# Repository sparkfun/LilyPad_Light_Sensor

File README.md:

LilyPad Light Sensor
========================================

[*LilyPad Light Sensor(DEV-14629)*](https://www.sparkfun.com/products/14629)

This is a simple to use light sensor that outputs an analog value from 0 to 5V. 
With exposure to daylight, this sensor will output 5V. 
Covering the sensor with your hand, the sensor will output 0V. 
In a normal indoor lighting situation, the sensor will output from 1 to 2V.

Repository Contents
-------------------
* **/Firmware** - Arduino Example Code
* **/Hardware** - Eagle design files (.brd, .sch)
* **/Production** - Production panel files (.brd)

Documentation
--------------
* **[Hookup Guide](https://learn.sparkfun.com/tutorials/lilypad-light-sensor-v2-hookup-guide)** - Basic hookup guide for the LilyPad Light Sensor.
* **[SparkFun Fritzing repo](https://github.com/sparkfun/Fritzing_Parts)** - Fritzing diagrams for SparkFun products.
* **[SparkFun 3D Model repo](https://github.com/sparkfun/3D_Models)** - 3D models of SparkFun products. 

License Information
-------------------
This product is _**open source**_! 

The **hardware** is released under [Creative Commons ShareAlike 4.0 International](https://creativecommons.org/licenses/by-sa/4.0/).

Please use, reuse, and modify these files as you see fit. Please maintain attribution to SparkFun Electronics and release anything derivative under the same license.

Distributed as-is; no warranty is given.

- Your friends at SparkFun.

_**Note:** A portion of this sale is given back to Dr. Leah Buechley for continued development and education of e-textiles._

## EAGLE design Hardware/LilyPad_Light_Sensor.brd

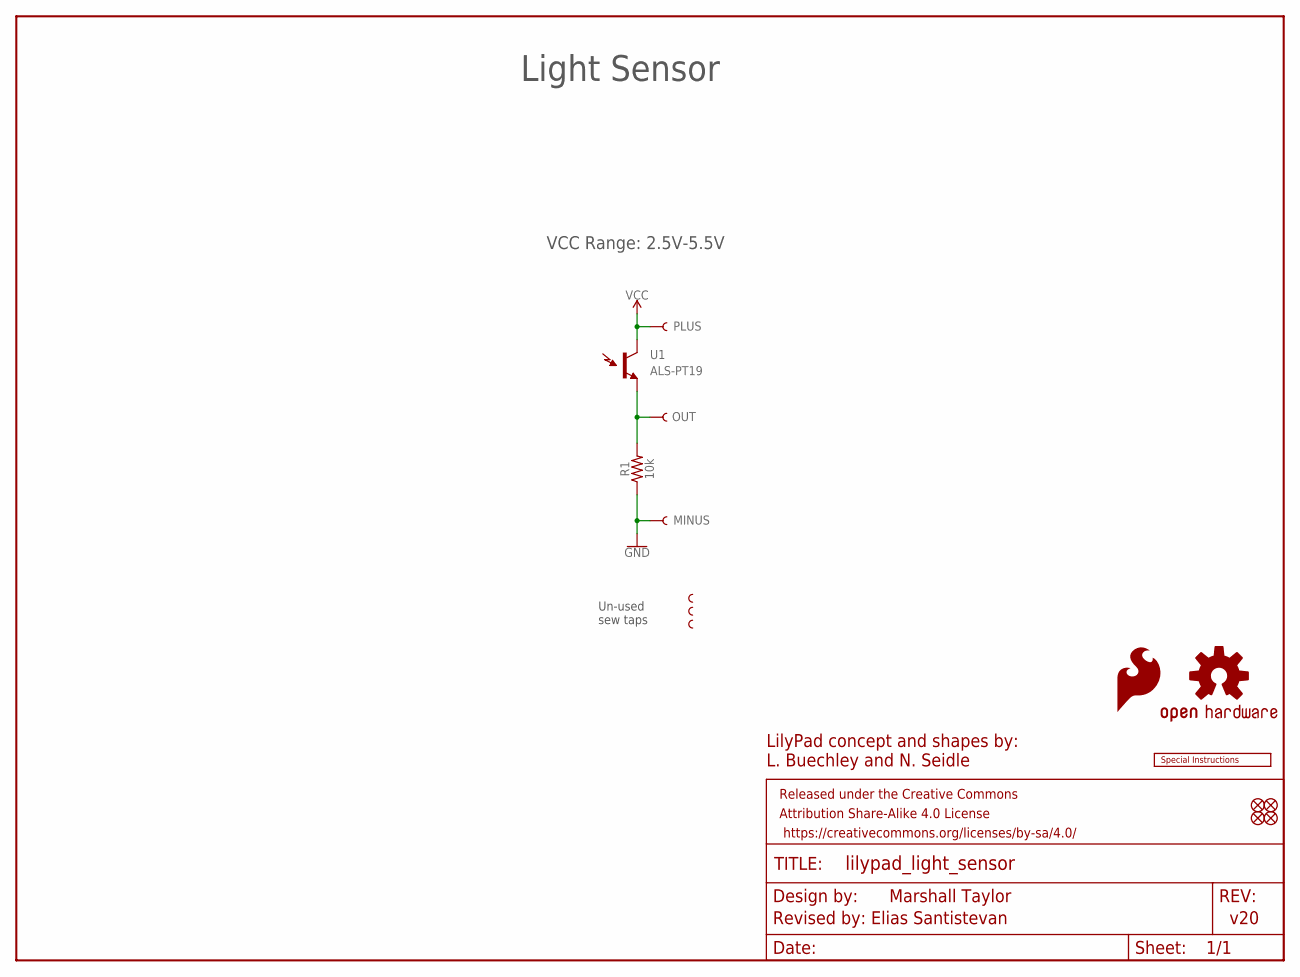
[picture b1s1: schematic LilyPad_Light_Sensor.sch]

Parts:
FD1, FD2, FD3, FD4: FIDUCIALUFIDUCIAL; FIDUCIAL-MICRO
FRAME2: FRAME-LETTER; CREATIVE_COMMONS
LOGO1: OSHW-LOGOMINI; OSHW-LOGO-MINI
LOGO2: SFE_LOGO_FLAME.1_INCH; SFE_LOGO_FLAME_.1
R1: 10k; 0603
SEWTAPLS+: PLUS; PETAL-SMALL-2SIDE
SEWTAPLS-: MINUS; PETAL-SMALL-2SIDE
SEWTAPLSOUT: OUT; PETAL-SMALL-2SIDE
ST1, ST2, ST3: SEWTAP-NOHOLE_SM_NH; PETAL-SMALL-NOHOLE
U1: ALS-PT19
U$1: SPECIAL_INSTRUCTIONS-ORDERING; ORDERING_INSTRUCTIONS

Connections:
3.3V: SEWTAPLS+.1, U1.C (C1)
D2: R1.2, SEWTAPLSOUT.1, U1.E (E1)
GND: R1.1, SEWTAPLS-.1

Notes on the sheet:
Un-used sew taps
Light Sensor
Marshall Taylor
v20
Revised by: Elias Santistevan
VCC Range: 2.5V-5.5V
LilyPad concept and shapes by: L. Buechley and N. Seidle

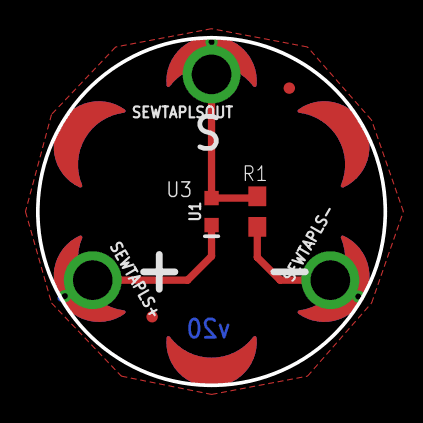
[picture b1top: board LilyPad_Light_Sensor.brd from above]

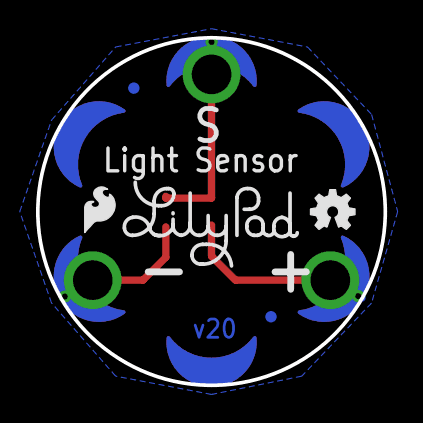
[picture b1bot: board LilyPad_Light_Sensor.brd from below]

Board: 2 copper layers, 19.3 x 19.3 mm, 17 parts (5 on the bottom side), 3 nets.

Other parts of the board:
U$5: LILYLOGO_SHORT; LILYPAD-WEARABLES_LOGO-LILYPAD

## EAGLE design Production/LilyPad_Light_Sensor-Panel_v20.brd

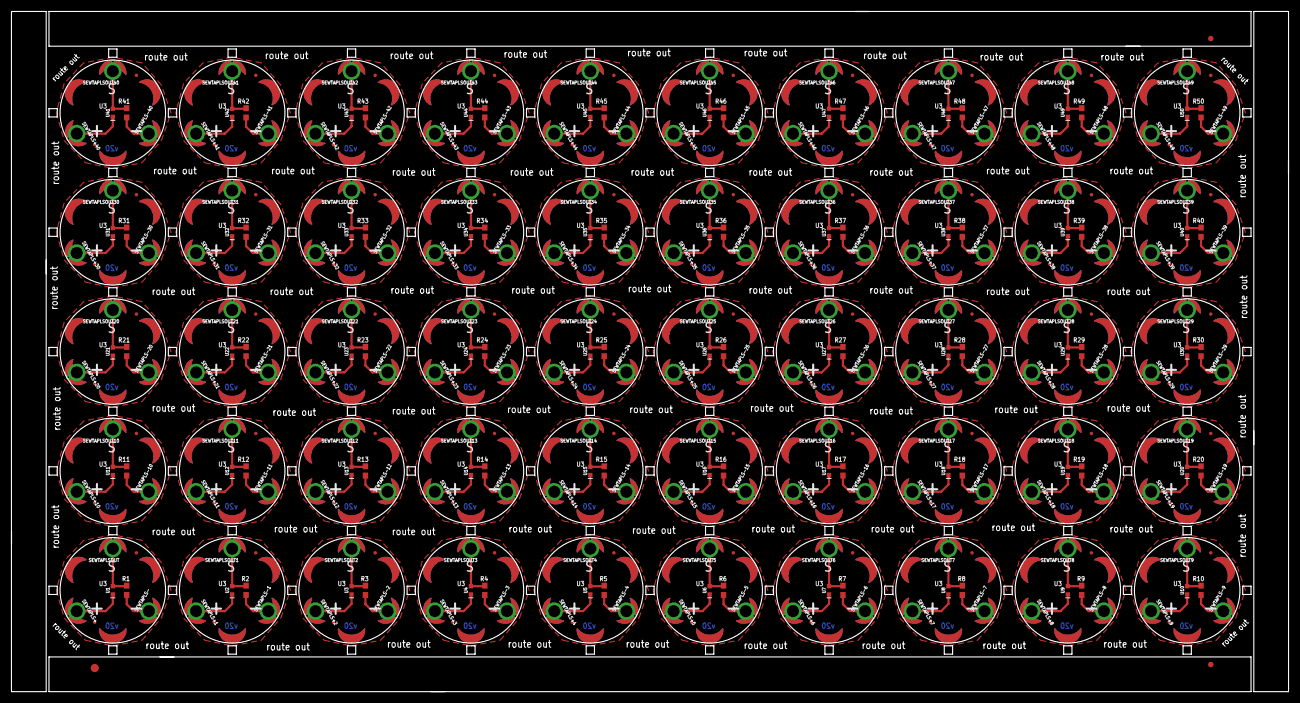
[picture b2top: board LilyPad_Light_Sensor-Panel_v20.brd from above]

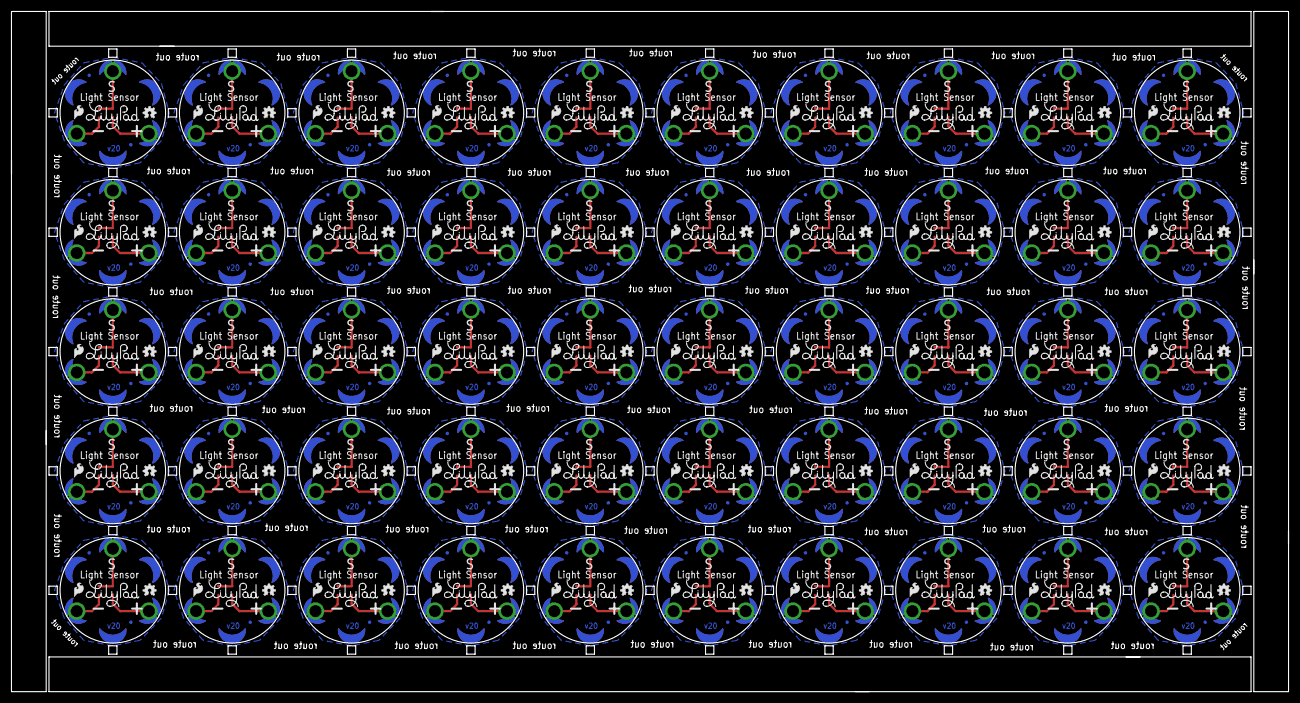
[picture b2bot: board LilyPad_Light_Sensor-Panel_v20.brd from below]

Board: 2 copper layers, 233.7 x 124.5 mm, 753 parts (250 on the bottom side), 150 nets.

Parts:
E$1: FIDUCIAL-1.5X3
E$5, E$8: FIDUCIAL-1X2
FD1, FD2, FD3, FD4, FD5, FD6, FD7, FD8, FD9, FD10, FD11, FD12, FD13, FD14, FD15, FD16, FD17, FD18, FD19, FD20, FD21, FD22, FD23, FD24, FD25, FD26, FD27, FD28, FD29, FD30, FD31, FD32, FD33, FD34, FD35, FD36, FD37, FD38, FD39, FD40, FD41, FD42, FD43, FD44, FD45, FD46, FD47, FD48, FD49, FD50, FD51, FD52, FD53, FD54, FD55, FD56, FD57, FD58, FD59, FD60, FD61, FD62, FD63, FD64, FD65, FD66, FD67, FD68, FD69, FD70, FD71, FD72, FD73, FD74, FD75, FD76, FD77, FD78, FD79, FD80, FD81, FD82, FD83, FD84, FD85, FD86, FD87, FD88, FD89, FD90, FD91, FD92, FD93, FD94, FD95, FD96, FD97, FD98, FD99, FD100, FD101, FD102, FD103, FD104, FD105, FD106, FD107, FD108, FD109, FD110, FD111, FD112, FD113, FD114, FD115, FD116, FD117, FD118, FD119, FD120, FD121, FD122, FD123, FD124, FD125, FD126, FD127, FD128, FD129, FD130, FD131, FD132, FD133, FD134, FD135, FD136, FD137, FD138, FD139, FD140, FD141, FD142, FD143, FD144, FD145, FD146, FD147, FD148, FD149, FD150, FD151, FD152, FD153, FD154, FD155, FD156, FD157, FD158, FD159, FD160, FD161, FD162, FD163, FD164, FD165, FD166, FD167, FD168, FD169, FD170, FD171, FD172, FD173, FD174, FD175, FD176, FD177, FD178, FD179, FD180, FD181, FD182, FD183, FD184, FD185, FD186, FD187, FD188, FD189, FD190, FD191, FD192, FD193, FD194, FD195, FD196, FD197, FD198, FD199, FD200: FIDUCIALUFIDUCIAL; FIDUCIAL-MICRO
LOGO1, LOGO3, LOGO5, LOGO7, LOGO9, LOGO11, LOGO13, LOGO15, LOGO17, LOGO19, LOGO21, LOGO23, LOGO25, LOGO27, LOGO29, LOGO31, LOGO33, LOGO35, LOGO37, LOGO39, LOGO41, LOGO43, LOGO45, LOGO47, LOGO49, LOGO51, LOGO53, LOGO55, LOGO57, LOGO59, LOGO61, LOGO63, LOGO65, LOGO67, LOGO69, LOGO71, LOGO73, LOGO75, LOGO77, LOGO79, LOGO81, LOGO83, LOGO85, LOGO87, LOGO89, LOGO91, LOGO93, LOGO95, LOGO97, LOGO99: OSHW-LOGOMINI; OSHW-LOGO-MINI
LOGO2, LOGO4, LOGO6, LOGO8, LOGO10, LOGO12, LOGO14, LOGO16, LOGO18, LOGO20, LOGO22, LOGO24, LOGO26, LOGO28, LOGO30, LOGO32, LOGO34, LOGO36, LOGO38, LOGO40, LOGO42, LOGO44, LOGO46, LOGO48, LOGO50, LOGO52, LOGO54, LOGO56, LOGO58, LOGO60, LOGO62, LOGO64, LOGO66, LOGO68, LOGO70, LOGO72, LOGO74, LOGO76, LOGO78, LOGO80, LOGO82, LOGO84, LOGO86, LOGO88, LOGO90, LOGO92, LOGO94, LOGO96, LOGO98, LOGO100: SFE_LOGO_FLAME.1_INCH; SFE_LOGO_FLAME_.1
R1, R2, R3, R4, R5, R6, R7, R8, R9, R10, R11, R12, R13, R14, R15, R16, R17, R18, R19, R20, R21, R22, R23, R24, R25, R26, R27, R28, R29, R30, R31, R32, R33, R34, R35, R36, R37, R38, R39, R40, R41, R42, R43, R44, R45, R46, R47, R48, R49, R50: 10k; 0603
SEWTAPLS+, SEWTAPLS+1, SEWTAPLS+2, SEWTAPLS+3, SEWTAPLS+4, SEWTAPLS+5, SEWTAPLS+6, SEWTAPLS+7, SEWTAPLS+8, SEWTAPLS+9, SEWTAPLS+10, SEWTAPLS+11, SEWTAPLS+12, SEWTAPLS+13, SEWTAPLS+14, SEWTAPLS+15, SEWTAPLS+16, SEWTAPLS+17, SEWTAPLS+18, SEWTAPLS+19, SEWTAPLS+20, SEWTAPLS+21, SEWTAPLS+22, SEWTAPLS+23, SEWTAPLS+24, SEWTAPLS+25, SEWTAPLS+26, SEWTAPLS+27, SEWTAPLS+28, SEWTAPLS+29, SEWTAPLS+30, SEWTAPLS+31, SEWTAPLS+32, SEWTAPLS+33, SEWTAPLS+34, SEWTAPLS+35, SEWTAPLS+36, SEWTAPLS+37, SEWTAPLS+38, SEWTAPLS+39, SEWTAPLS+40, SEWTAPLS+41, SEWTAPLS+42, SEWTAPLS+43, SEWTAPLS+44, SEWTAPLS+45, SEWTAPLS+46, SEWTAPLS+47, SEWTAPLS+48, SEWTAPLS+49: PLUS; PETAL-SMALL-2SIDE
SEWTAPLS-, SEWTAPLS-1, SEWTAPLS-2, SEWTAPLS-3, SEWTAPLS-4, SEWTAPLS-5, SEWTAPLS-6, SEWTAPLS-7, SEWTAPLS-8, SEWTAPLS-9, SEWTAPLS-10, SEWTAPLS-11, SEWTAPLS-12, SEWTAPLS-13, SEWTAPLS-14, SEWTAPLS-15, SEWTAPLS-16, SEWTAPLS-17, SEWTAPLS-18, SEWTAPLS-19, SEWTAPLS-20, SEWTAPLS-21, SEWTAPLS-22, SEWTAPLS-23, SEWTAPLS-24, SEWTAPLS-25, SEWTAPLS-26, SEWTAPLS-27, SEWTAPLS-28, SEWTAPLS-29, SEWTAPLS-30, SEWTAPLS-31, SEWTAPLS-32, SEWTAPLS-33, SEWTAPLS-34, SEWTAPLS-35, SEWTAPLS-36, SEWTAPLS-37, SEWTAPLS-38, SEWTAPLS-39, SEWTAPLS-40, SEWTAPLS-41, SEWTAPLS-42, SEWTAPLS-43, SEWTAPLS-44, SEWTAPLS-45, SEWTAPLS-46, SEWTAPLS-47, SEWTAPLS-48, SEWTAPLS-49: MINUS; PETAL-SMALL-2SIDE
SEWTAPLSOUT, SEWTAPLSOUT1, SEWTAPLSOUT2, SEWTAPLSOUT3, SEWTAPLSOUT4, SEWTAPLSOUT5, SEWTAPLSOUT6, SEWTAPLSOUT7, SEWTAPLSOUT8, SEWTAPLSOUT9, SEWTAPLSOUT10, SEWTAPLSOUT11, SEWTAPLSOUT12, SEWTAPLSOUT13, SEWTAPLSOUT14, SEWTAPLSOUT15, SEWTAPLSOUT16, SEWTAPLSOUT17, SEWTAPLSOUT18, SEWTAPLSOUT19, SEWTAPLSOUT20, SEWTAPLSOUT21, SEWTAPLSOUT22, SEWTAPLSOUT23, SEWTAPLSOUT24, SEWTAPLSOUT25, SEWTAPLSOUT26, SEWTAPLSOUT27, SEWTAPLSOUT28, SEWTAPLSOUT29, SEWTAPLSOUT30, SEWTAPLSOUT31, SEWTAPLSOUT32, SEWTAPLSOUT33, SEWTAPLSOUT34, SEWTAPLSOUT35, SEWTAPLSOUT36, SEWTAPLSOUT37, SEWTAPLSOUT38, SEWTAPLSOUT39, SEWTAPLSOUT40, SEWTAPLSOUT41, SEWTAPLSOUT42, SEWTAPLSOUT43, SEWTAPLSOUT44, SEWTAPLSOUT45, SEWTAPLSOUT46, SEWTAPLSOUT47, SEWTAPLSOUT48, SEWTAPLSOUT49: OUT; PETAL-SMALL-2SIDE
ST1, ST2, ST3, ST4, ST5, ST6, ST7, ST8, ST9, ST10, ST11, ST12, ST13, ST14, ST15, ST16, ST17, ST18, ST19, ST20, ST21, ST22, ST23, ST24, ST25, ST26, ST27, ST28, ST29, ST30, ST31, ST32, ST33, ST34, ST35, ST36, ST37, ST38, ST39, ST40, ST41, ST42, ST43, ST44, ST45, ST46, ST47, ST48, ST49, ST50, ST51, ST52, ST53, ST54, ST55, ST56, ST57, ST58, ST59, ST60, ST61, ST62, ST63, ST64, ST65, ST66, ST67, ST68, ST69, ST70, ST71, ST72, ST73, ST74, ST75, ST76, ST77, ST78, ST79, ST80, ST81, ST82, ST83, ST84, ST85, ST86, ST87, ST88, ST89, ST90, ST91, ST92, ST93, ST94, ST95, ST96, ST97, ST98, ST99, ST100, ST101, ST102, ST103, ST104, ST105, ST106, ST107, ST108, ST109, ST110, ST111, ST112, ST113, ST114, ST115, ST116, ST117, ST118, ST119, ST120, ST121, ST122, ST123, ST124, ST125, ST126, ST127, ST128, ST129, ST130, ST131, ST132, ST133, ST134, ST135, ST136, ST137, ST138, ST139, ST140, ST141, ST142, ST143, ST144, ST145, ST146, ST147, ST148, ST149, ST150: SEWTAP-NOHOLE_SM_NH; PETAL-SMALL-NOHOLE
U1, U2, U3, U4, U5, U6, U7, U8, U9, U10, U11, U12, U13, U14, U15, U16, U17, U18, U19, U20, U21, U22, U23, U24, U25, U26, U27, U28, U29, U30, U31, U32, U33, U34, U35, U36, U37, U38, U39, U40, U41, U42, U43, U44, U45, U46, U47, U48, U49, U50: ALS-PT19
U$1, U$2, U$3, U$4, U$5, U$6, U$7, U$8, U$9, U$10, U$11, U$12, U$13, U$14, U$15, U$16, U$17, U$18, U$19, U$20, U$21, U$22, U$23, U$24, U$25, U$26, U$27, U$28, U$29, U$30, U$31, U$32, U$33, U$34, U$35, U$36, U$37, U$38, U$39, U$40, U$41, U$42, U$43, U$44, U$45, U$46, U$47, U$48, U$49, U$50: LILYLOGO_SHORT; LILYPAD-WEARABLES_LOGO-LILYPAD

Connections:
3.3V: SEWTAPLS+.1, U1.C
3.3V1: SEWTAPLS+1.1, U2.C
3.3V2: SEWTAPLS+2.1, U3.C
3.3V3: SEWTAPLS+3.1, U4.C
3.3V4: SEWTAPLS+4.1, U5.C
3.3V5: SEWTAPLS+5.1, U6.C
3.3V6: SEWTAPLS+6.1, U7.C
3.3V7: SEWTAPLS+7.1, U8.C
3.3V8: SEWTAPLS+8.1, U9.C
3.3V9: SEWTAPLS+9.1, U10.C
3.3V10: SEWTAPLS+10.1, U11.C
3.3V11: SEWTAPLS+11.1, U12.C
3.3V12: SEWTAPLS+12.1, U13.C
3.3V13: SEWTAPLS+13.1, U14.C
3.3V14: SEWTAPLS+14.1, U15.C
3.3V15: SEWTAPLS+15.1, U16.C
3.3V16: SEWTAPLS+16.1, U17.C
3.3V17: SEWTAPLS+17.1, U18.C
3.3V18: SEWTAPLS+18.1, U19.C
3.3V19: SEWTAPLS+19.1, U20.C
3.3V20: SEWTAPLS+20.1, U21.C
3.3V21: SEWTAPLS+21.1, U22.C
3.3V22: SEWTAPLS+22.1, U23.C
3.3V23: SEWTAPLS+23.1, U24.C
3.3V24: SEWTAPLS+24.1, U25.C
3.3V25: SEWTAPLS+25.1, U26.C
3.3V26: SEWTAPLS+26.1, U27.C
3.3V27: SEWTAPLS+27.1, U28.C
3.3V28: SEWTAPLS+28.1, U29.C
3.3V29: SEWTAPLS+29.1, U30.C
3.3V30: SEWTAPLS+30.1, U31.C
3.3V31: SEWTAPLS+31.1, U32.C
3.3V32: SEWTAPLS+32.1, U33.C
3.3V33: SEWTAPLS+33.1, U34.C
3.3V34: SEWTAPLS+34.1, U35.C
3.3V35: SEWTAPLS+35.1, U36.C
3.3V36: SEWTAPLS+36.1, U37.C
3.3V37: SEWTAPLS+37.1, U38.C
3.3V38: SEWTAPLS+38.1, U39.C
3.3V39: SEWTAPLS+39.1, U40.C
3.3V40: SEWTAPLS+40.1, U41.C
3.3V41: SEWTAPLS+41.1, U42.C
3.3V42: SEWTAPLS+42.1, U43.C
3.3V43: SEWTAPLS+43.1, U44.C
3.3V44: SEWTAPLS+44.1, U45.C
3.3V45: SEWTAPLS+45.1, U46.C
3.3V46: SEWTAPLS+46.1, U47.C
3.3V47: SEWTAPLS+47.1, U48.C
3.3V48: SEWTAPLS+48.1, U49.C
3.3V49: SEWTAPLS+49.1, U50.C
D1: R2.2, SEWTAPLSOUT1.1, U2.E
D2: R1.2, SEWTAPLSOUT.1, U1.E
D3: R3.2, SEWTAPLSOUT2.1, U3.E
D4: R4.2, SEWTAPLSOUT3.1, U4.E
D5: R5.2, SEWTAPLSOUT4.1, U5.E
D6: R6.2, SEWTAPLSOUT5.1, U6.E
D7: R7.2, SEWTAPLSOUT6.1, U7.E
D8: R8.2, SEWTAPLSOUT7.1, U8.E
D9: R9.2, SEWTAPLSOUT8.1, U9.E
D10: R10.2, SEWTAPLSOUT9.1, U10.E
D11: R11.2, SEWTAPLSOUT10.1, U11.E
D12: R12.2, SEWTAPLSOUT11.1, U12.E
D13: R13.2, SEWTAPLSOUT12.1, U13.E
D14: R14.2, SEWTAPLSOUT13.1, U14.E
D15: R15.2, SEWTAPLSOUT14.1, U15.E
D16: R16.2, SEWTAPLSOUT15.1, U16.E
D17: R17.2, SEWTAPLSOUT16.1, U17.E
D18: R18.2, SEWTAPLSOUT17.1, U18.E
D19: R19.2, SEWTAPLSOUT18.1, U19.E
D20: R20.2, SEWTAPLSOUT19.1, U20.E
D21: R21.2, SEWTAPLSOUT20.1, U21.E
D22: R22.2, SEWTAPLSOUT21.1, U22.E
D23: R23.2, SEWTAPLSOUT22.1, U23.E
D24: R24.2, SEWTAPLSOUT23.1, U24.E
D25: R25.2, SEWTAPLSOUT24.1, U25.E
D26: R26.2, SEWTAPLSOUT25.1, U26.E
D27: R27.2, SEWTAPLSOUT26.1, U27.E
D28: R28.2, SEWTAPLSOUT27.1, U28.E
D29: R29.2, SEWTAPLSOUT28.1, U29.E
D30: R30.2, SEWTAPLSOUT29.1, U30.E
D31: R31.2, SEWTAPLSOUT30.1, U31.E
D32: R32.2, SEWTAPLSOUT31.1, U32.E
D33: R33.2, SEWTAPLSOUT32.1, U33.E
D34: R34.2, SEWTAPLSOUT33.1, U34.E
D35: R35.2, SEWTAPLSOUT34.1, U35.E
D36: R36.2, SEWTAPLSOUT35.1, U36.E
D37: R37.2, SEWTAPLSOUT36.1, U37.E
D38: R38.2, SEWTAPLSOUT37.1, U38.E
D39: R39.2, SEWTAPLSOUT38.1, U39.E
D40: R40.2, SEWTAPLSOUT39.1, U40.E
D41: R41.2, SEWTAPLSOUT40.1, U41.E
D42: R42.2, SEWTAPLSOUT41.1, U42.E
D43: R43.2, SEWTAPLSOUT42.1, U43.E
D44: R44.2, SEWTAPLSOUT43.1, U44.E
D45: R45.2, SEWTAPLSOUT44.1, U45.E
D46: R46.2, SEWTAPLSOUT45.1, U46.E
D47: R47.2, SEWTAPLSOUT46.1, U47.E
D48: R48.2, SEWTAPLSOUT47.1, U48.E
D49: R49.2, SEWTAPLSOUT48.1, U49.E
D50: R50.2, SEWTAPLSOUT49.1, U50.E
GND: R1.1, SEWTAPLS-.1
GND1: R2.1, SEWTAPLS-1.1
GND2: R3.1, SEWTAPLS-2.1
GND3: R4.1, SEWTAPLS-3.1
GND4: R5.1, SEWTAPLS-4.1
GND5: R6.1, SEWTAPLS-5.1
GND6: R7.1, SEWTAPLS-6.1
GND7: R8.1, SEWTAPLS-7.1
GND8: R9.1, SEWTAPLS-8.1
GND9: R10.1, SEWTAPLS-9.1
GND10: R11.1, SEWTAPLS-10.1
GND11: R12.1, SEWTAPLS-11.1
GND12: R13.1, SEWTAPLS-12.1
GND13: R14.1, SEWTAPLS-13.1
GND14: R15.1, SEWTAPLS-14.1
GND15: R16.1, SEWTAPLS-15.1
GND16: R17.1, SEWTAPLS-16.1
GND17: R18.1, SEWTAPLS-17.1
GND18: R19.1, SEWTAPLS-18.1
GND19: R20.1, SEWTAPLS-19.1
GND20: R21.1, SEWTAPLS-20.1
GND21: R22.1, SEWTAPLS-21.1
GND22: R23.1, SEWTAPLS-22.1
GND23: R24.1, SEWTAPLS-23.1
GND24: R25.1, SEWTAPLS-24.1
GND25: R26.1, SEWTAPLS-25.1
GND26: R27.1, SEWTAPLS-26.1
GND27: R28.1, SEWTAPLS-27.1
GND28: R29.1, SEWTAPLS-28.1
GND29: R30.1, SEWTAPLS-29.1
GND30: R31.1, SEWTAPLS-30.1
GND31: R32.1, SEWTAPLS-31.1
GND32: R33.1, SEWTAPLS-32.1
GND33: R34.1, SEWTAPLS-33.1
GND34: R35.1, SEWTAPLS-34.1
GND35: R36.1, SEWTAPLS-35.1
GND36: R37.1, SEWTAPLS-36.1
GND37: R38.1, SEWTAPLS-37.1
GND38: R39.1, SEWTAPLS-38.1
GND39: R40.1, SEWTAPLS-39.1
GND40: R41.1, SEWTAPLS-40.1
GND41: R42.1, SEWTAPLS-41.1
GND42: R43.1, SEWTAPLS-42.1
GND43: R44.1, SEWTAPLS-43.1
GND44: R45.1, SEWTAPLS-44.1
GND45: R46.1, SEWTAPLS-45.1
GND46: R47.1, SEWTAPLS-46.1
GND47: R48.1, SEWTAPLS-47.1
GND48: R49.1, SEWTAPLS-48.1
GND49: R50.1, SEWTAPLS-49.1

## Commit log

2015-05-05 adding hardware, updating README
2018-01-23 Update README.md
    Linking tutorial.
2018-01-23 Create ReadingLight.ino
    Adding Angela's Example Code.
2018-01-23 Create LightTrigger.ino
    Adding Angela's Example Code.
2018-02-12 Cleaned up some things
    Read for review
2018-02-21 Small changes after review
    "Revised by:" added to schematic and version number fixed.
2018-02-22 Fiducials, VCC Range added
2018-03-02 Fixes from double check
2018-03-30 Double Check changes!
2018-04-05 created panel v20
2018-06-08 Updating ReadMe for V2
    Updating ReadMe for V2

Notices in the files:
parts and their libraries:
SparkFun-Aesthetics: Licensing: CC v3.0 Share-Alike You are welcome to use this library for commercial purposes.
SparkFun-Aesthetics: Released under the Creative Commons Attribution Share-Alike 4.0 License
SparkFun-Aesthetics: Released under the Creative Commons
